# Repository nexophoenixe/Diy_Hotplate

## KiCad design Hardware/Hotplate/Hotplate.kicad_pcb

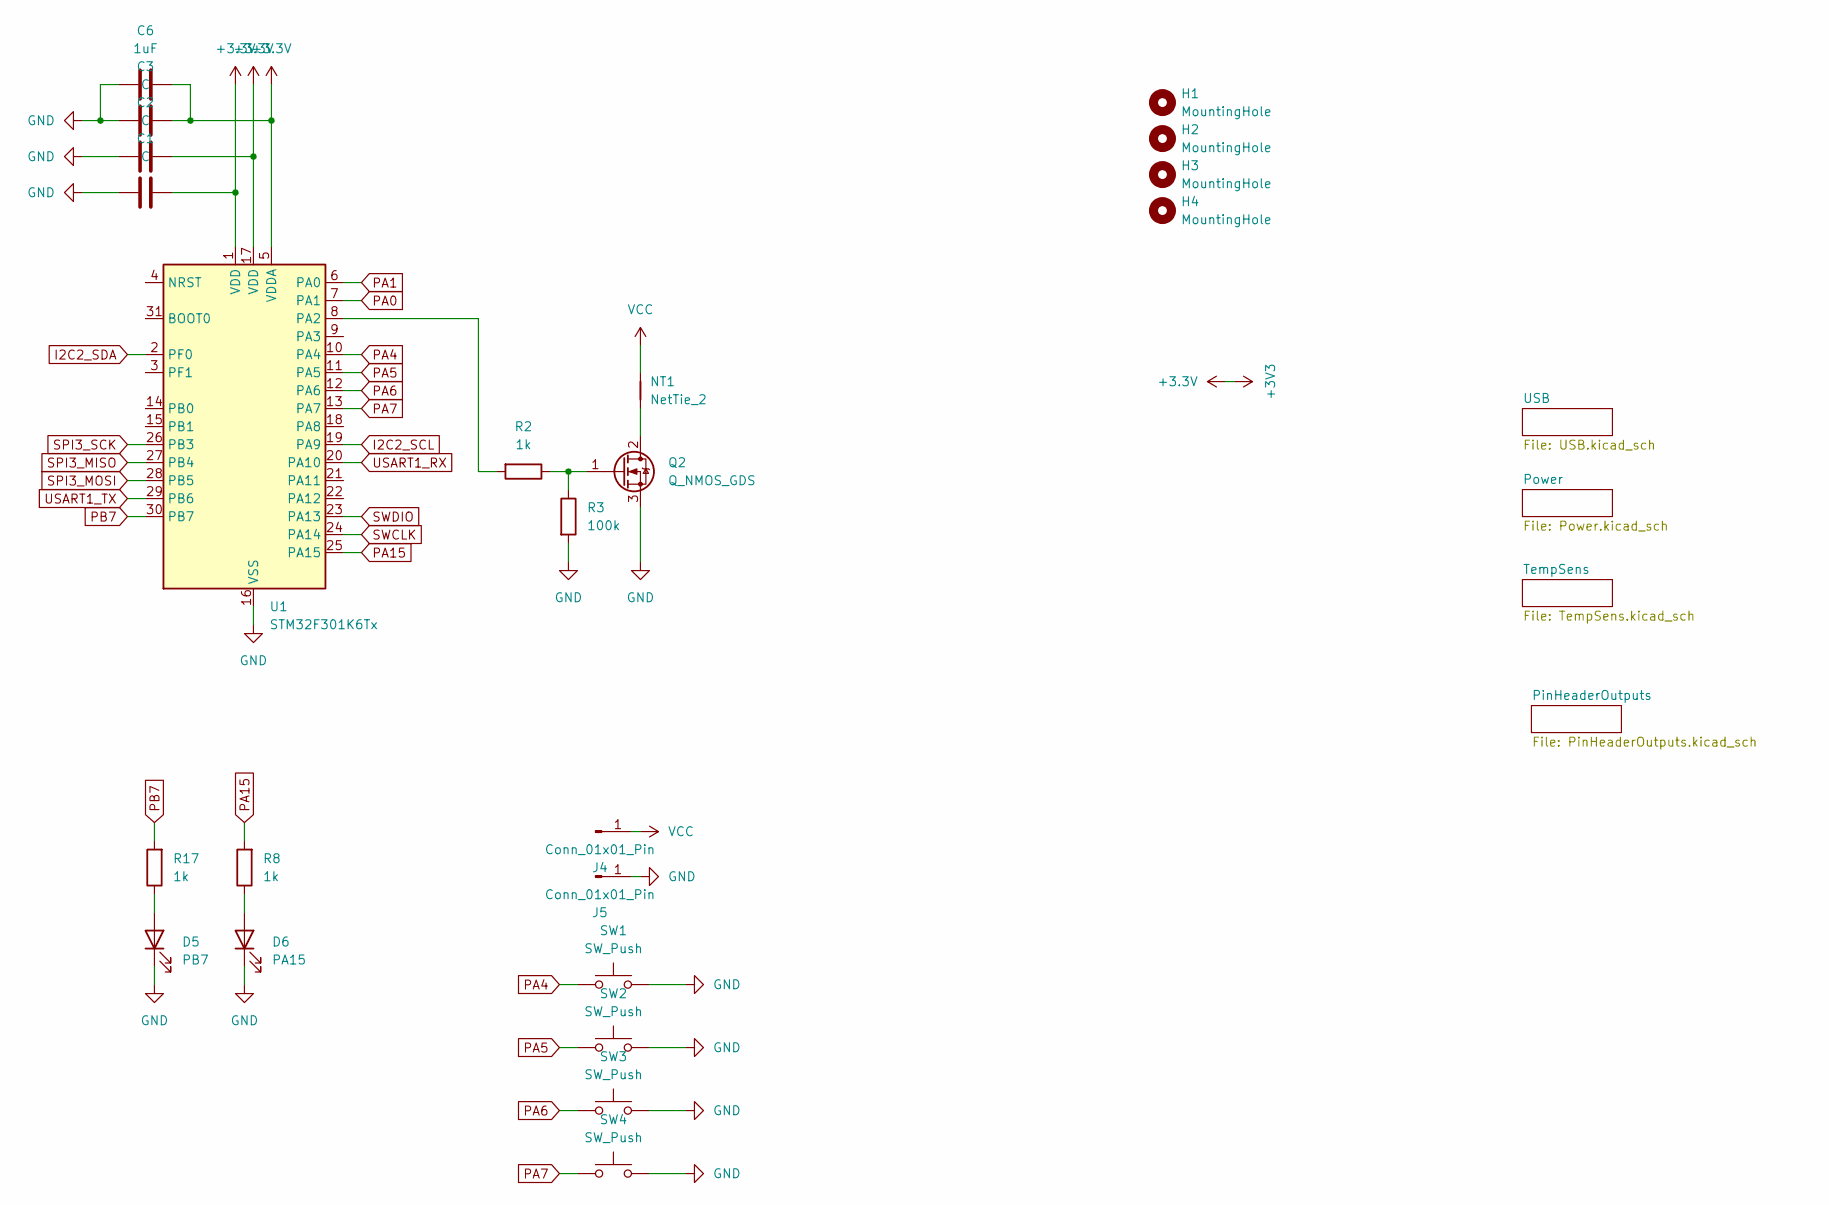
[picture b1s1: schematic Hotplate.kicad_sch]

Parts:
C1, C2, C3: C; C_0603_1608Metric
C6: 1uF; C_0603_1608Metric
D5: PB7; LED_0603_1608Metric_Pad1.05x0.95mm_HandSolder
D6: PA15; LED_0603_1608Metric_Pad1.05x0.95mm_HandSolder
H1, H2, H3, H4: MountingHole; MountingHole_2.7mm_M2.5
J4, J5: Conn_01x01_Pin; SolderWire-1.5sqmm_1x01_D1.7mm_OD3mm
NT1: NetTie_2; NetTie-2_SMD_Pad2.0mm
Q2: Q_NMOS_GDS; TO-252-2
R2: 1k; R_0805_2012Metric
R3: 100k; R_0805_2012Metric
R8, R17: 1k; R_0603_1608Metric_Pad0.98x0.95mm_HandSolder
SW1, SW2, SW3, SW4: SW_Push; SW_PUSH_6mm
U1: STM32F301K6Tx; LQFP-32_7x7mm_P0.8mm

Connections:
+3.3V: C1.2, C2.2, C3.2, C6.2, U1.1 (VDD), U1.5 (VDDA), U1.17 (VDD); also elsewhere on the board
GND: C1.1, C2.1, C3.1, C6.1, D5.1 (K), D6.1 (K), J5.1, Q2.3 (S), R3.2, SW1.2, SW2.2, SW3.2, SW4.2, U1.16 (VSS), U1.32 (VSS); also elsewhere on the board
I2C2_SCL: U1.19 (PA9); also elsewhere on the board
I2C2_SDA: U1.2 (PF0); also elsewhere on the board
unnamed: D5.2 (A), R17.1
unnamed: D6.2 (A), R8.1
unnamed: NT1.1, Q2.2 (D)
unnamed: Q2.1 (G), R2.1, R3.1
unnamed: R2.2, U1.8 (PA2)
PA0: U1.7 (PA1); also elsewhere on the board
PA1: U1.6 (PA0); also elsewhere on the board
PA4: SW1.1, U1.10 (PA4)
PA5: SW2.1, U1.11 (PA5)
PA6: SW3.1, U1.12 (PA6)
PA7: SW4.1, U1.13 (PA7)
PA15: R8.2, U1.25 (PA15)
PB7: R17.2, U1.30 (PB7)
SPI3_MISO: U1.27 (PB4); also elsewhere on the board
SPI3_MOSI: U1.28 (PB5); also elsewhere on the board
SPI3_SCK: U1.26 (PB3); also elsewhere on the board
SWCLK: U1.24 (PA14); also elsewhere on the board
SWDIO: U1.23 (PA13); also elsewhere on the board
USART1_RX: U1.20 (PA10); also elsewhere on the board
USART1_TX: U1.29 (PB6); also elsewhere on the board
VCC: J4.1, NT1.2; also elsewhere on the board

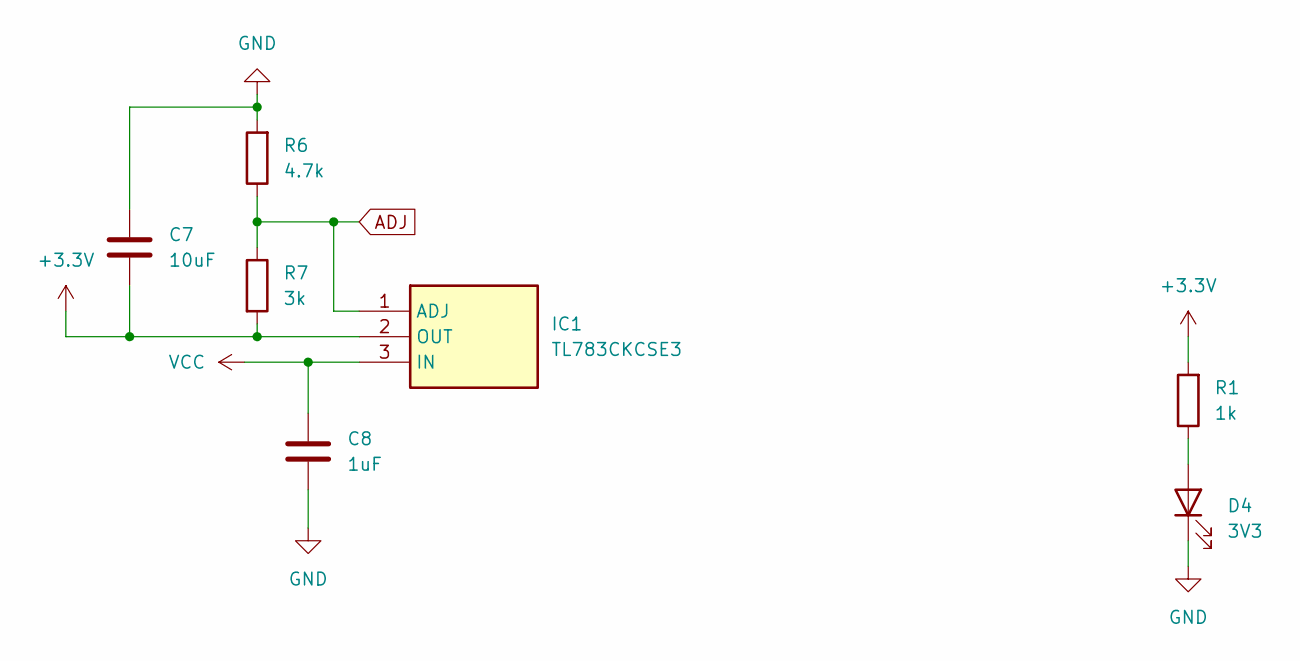
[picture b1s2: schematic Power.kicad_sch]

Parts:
C7: 10uF; C_0805_2012Metric; LCSC C15849
C8: 1uF; C_0805_2012Metric; LCSC C15849
D4: 3V3; LED_0603_1608Metric_Pad1.05x0.95mm_HandSolder
IC1: TL783CKCSE3; TO254P470X1016X1965-3P; Mouser Part Number 595-TL783CKCSE3
R1: 1k; R_0603_1608Metric_Pad0.98x0.95mm_HandSolder
R6: 4.7k; R_0805_2012Metric
R7: 3k; R_0805_2012Metric

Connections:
+3.3V: C7.2, IC1.2 (OUT), R1.2, R7.2; also elsewhere on the board
ADJ: IC1.1 (ADJ), R6.1, R7.1
GND: C7.1, C8.2, D4.1 (K), R6.2; also elsewhere on the board
unnamed: D4.2 (A), R1.1
VCC: C8.1, IC1.3 (IN); also elsewhere on the board

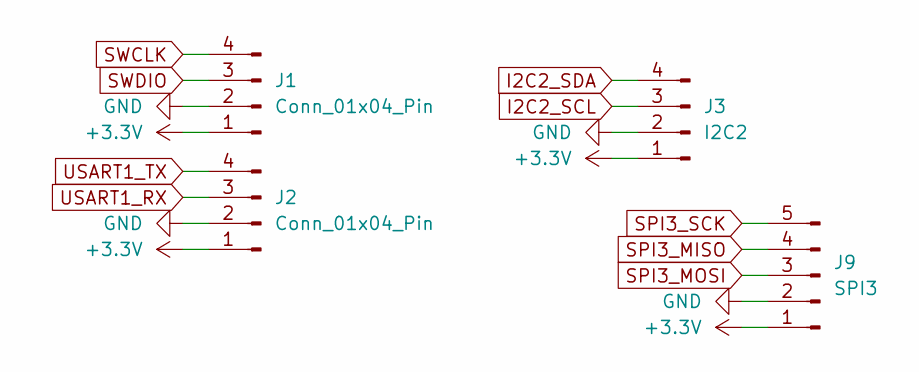
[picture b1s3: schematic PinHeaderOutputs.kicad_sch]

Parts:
J1, J2: Conn_01x04_Pin; PinHeader_1x04_P2.54mm_Vertical
J3: I2C2; PinHeader_1x04_P2.54mm_Vertical
J9: SPI3; PinHeader_1x05_P2.54mm_Vertical

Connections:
+3.3V: J1.1, J2.1, J3.1, J9.1; also elsewhere on the board
GND: J1.2, J2.2, J3.2, J9.2; also elsewhere on the board
I2C2_SCL: J3.3; also elsewhere on the board
I2C2_SDA: J3.4; also elsewhere on the board
SPI3_MISO: J9.4; also elsewhere on the board
SPI3_MOSI: J9.3; also elsewhere on the board
SPI3_SCK: J9.5; also elsewhere on the board
SWCLK: J1.4; also elsewhere on the board
SWDIO: J1.3; also elsewhere on the board
USART1_RX: J2.3; also elsewhere on the board
USART1_TX: J2.4; also elsewhere on the board

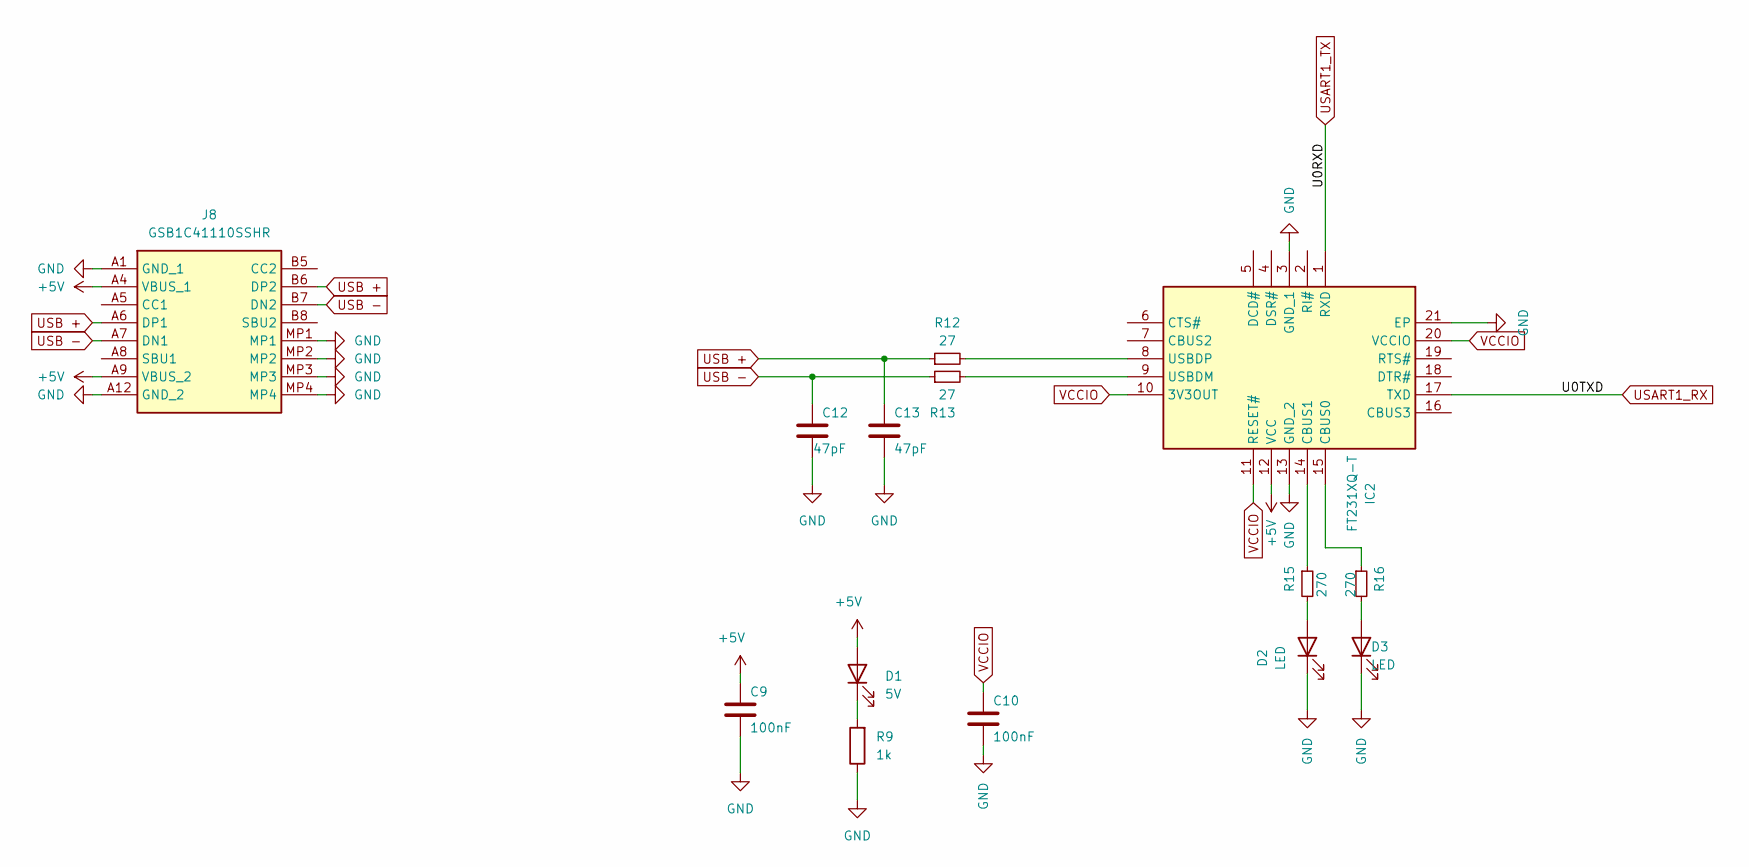
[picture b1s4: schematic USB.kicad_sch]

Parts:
C9, C10: 100nF; C_0603_1608Metric_Pad1.08x0.95mm_HandSolder
C12, C13: 47pF; C_0603_1608Metric_Pad1.08x0.95mm_HandSolder
D1: 5V; LED_0603_1608Metric_Pad1.05x0.95mm_HandSolder
D2, D3: LED; LED_0603_1608Metric_Pad1.05x0.95mm_HandSolder
IC2: FT231XQ-T; QFN50P400X400X80-21N; Mouser Part Number 895-FT231XQ-T
J8: GSB1C41110SSHR; Manufacturer_Part_Number GSB1C41110SSHR
R9: 1k; R_0603_1608Metric_Pad0.98x0.95mm_HandSolder
R12, R13: 27; R_0603_1608Metric_Pad0.98x0.95mm_HandSolder
R15, R16: 270; R_0603_1608Metric_Pad0.98x0.95mm_HandSolder

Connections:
+5V: C9.1, D1.2 (A), IC2.12 (VCC), J8.A4 (VBUS_1), J8.A9 (VBUS_2)
GND: C9.2, C10.2, C12.2, C13.2, D2.1 (K), D3.1 (K), IC2.3 (GND_1), IC2.13 (GND_2), IC2.21 (EP), J8.A1 (GND_1), J8.A12 (GND_2), J8.MP1, J8.MP2, J8.MP3, J8.MP4, R9.1; also elsewhere on the board
unnamed: D1.1 (K), R9.2
unnamed: D2.2 (A), R15.2
unnamed: D3.2 (A), R16.2
unnamed: IC2.15 (CBUS0), R16.1
unnamed: IC2.14 (CBUS1), R15.1
unnamed: IC2.9 (USBDM), R13.2
unnamed: IC2.8 (USBDP), R12.2
USART1_RX: IC2.17 (TXD); also elsewhere on the board
USART1_TX: IC2.1 (RXD); also elsewhere on the board
USB +: C13.1, J8.A6 (DP1), J8.B6 (DP2), R12.1
USB -: C12.1, J8.A7 (DN1), J8.B7 (DN2), R13.1
VCCIO: C10.1, IC2.10 (3V3OUT), IC2.11 (RESET#), IC2.20 (VCCIO)

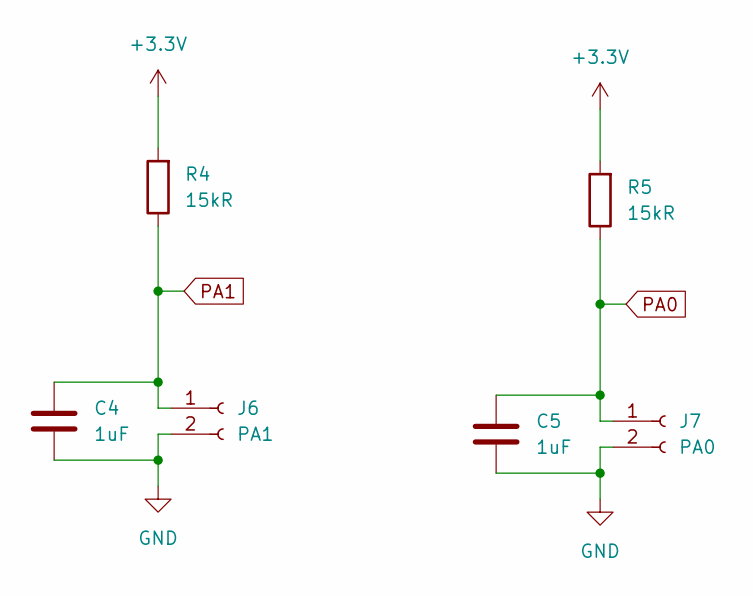
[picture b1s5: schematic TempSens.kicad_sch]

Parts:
C4, C5: 1uF; C_0603_1608Metric; LCSC C15849
J6: PA1; JST_EH_B2B-EH-A_1x02_P2.50mm_Vertical
J7: PA0; JST_EH_B2B-EH-A_1x02_P2.50mm_Vertical
R4, R5: 15kR; R_0805_2012Metric; LCSC C17475

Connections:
+3.3V: R4.2, R5.2; also elsewhere on the board
GND: C4.2, C5.2, J6.2, J7.2; also elsewhere on the board
PA0: C5.1, J7.1, R5.1; also elsewhere on the board
PA1: C4.1, J6.1, R4.1; also elsewhere on the board

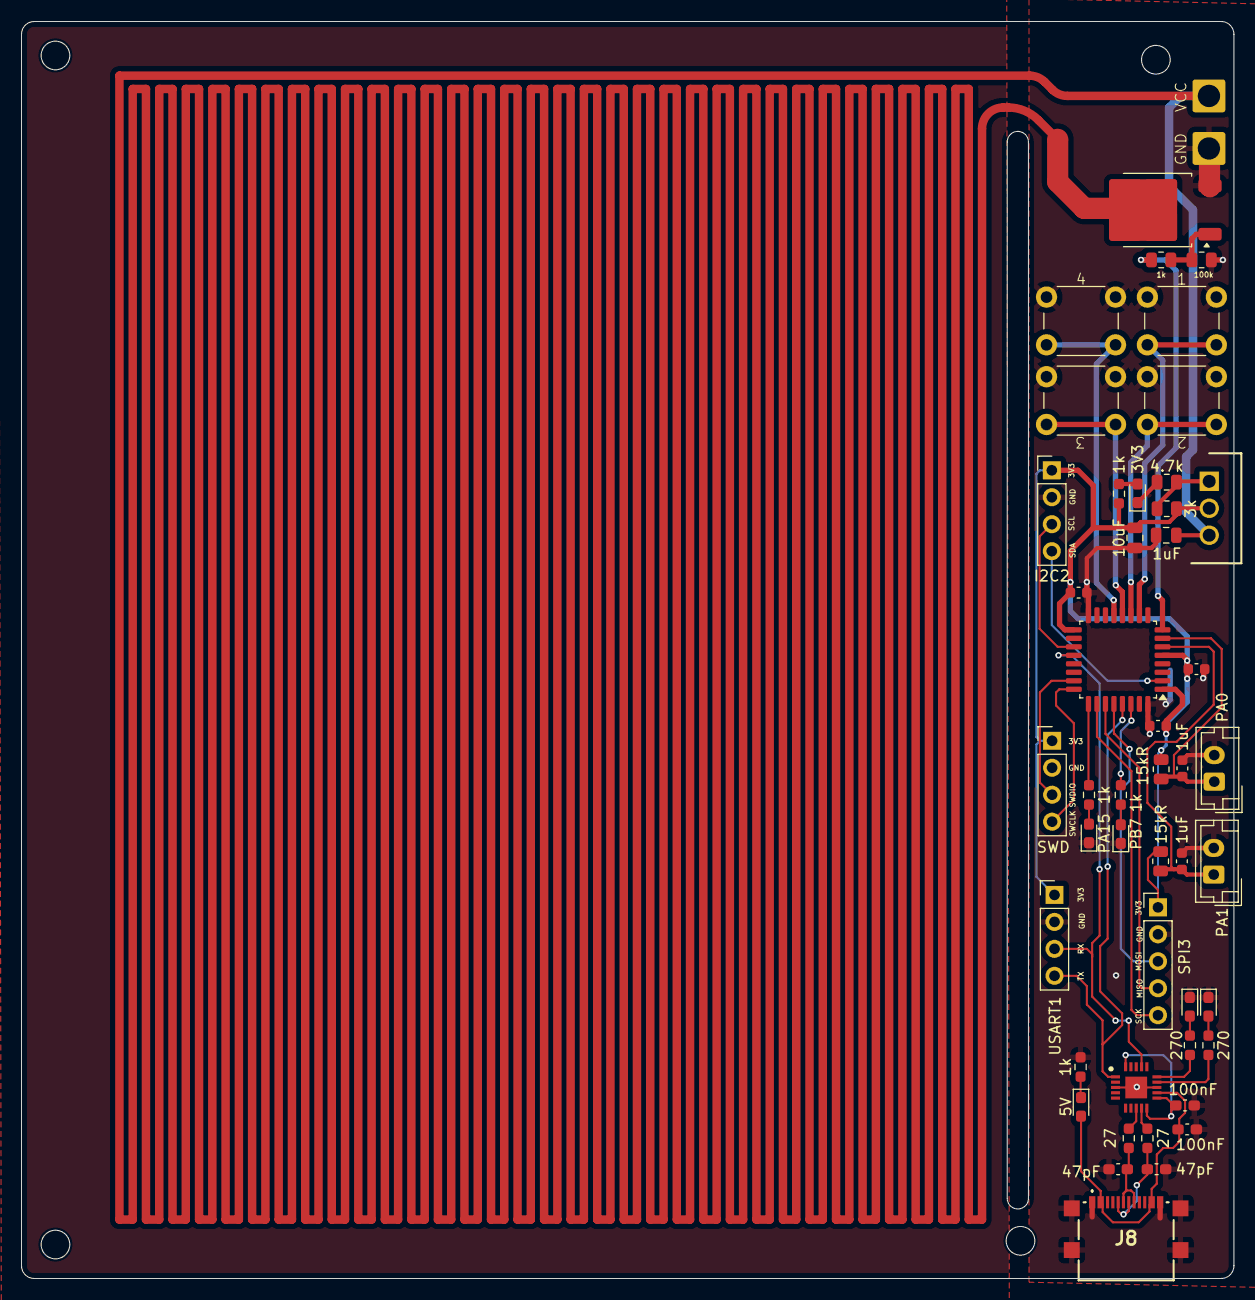
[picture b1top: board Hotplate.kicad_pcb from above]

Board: 2 copper layers, 114.2 x 118.4 mm, 54 parts (1 on the bottom side), 38 nets.

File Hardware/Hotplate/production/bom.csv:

Designator,Footprint,Quantity,Value,LCSC Part #
"C1, C2, C3",0603,3,C,
"C10, C9",0603,2,100nF,
"C12, C13",0603,2,47pF,
"C4, C5",0603,2,1uF,C15849
C6,0603,1,1uF,
C7,0805,1,10uF,C15849
C8,0805,1,1uF,C15849
D1,0603,1,5V,
"D2, D3",0603,2,LED,
D4,0603,1,3V3,
D5,0603,1,PB7,
D6,0603,1,PA15,
IC1,TO254P470X1016X1965-3P,1,TL783CKCSE3,
IC2,QFN50P400X400X80-21N,1,FT231XQ-T,
"J1, J2",PinHeader_1x04_P2.54mm_Vertical,2,Conn_01x04_Pin,
J3,PinHeader_1x04_P2.54mm_Vertical,1,I2C2,
"J4, J5",SolderWire-1.5sqmm_1x01_D1.7mm_OD3mm,2,Conn_01x01_Pin,
J8,GSB1C41110SSHR,1,GSB1C41110SSHR,
J9,PinHeader_1x05_P2.54mm_Vertical,1,SPI3,
Q2,TO-252-2,1,Q_NMOS_GDS,
"R1, R17, R8, R9",0603,4,1k,
"R12, R13",0603,2,27,
"R15, R16",0603,2,270,
R2,0805,1,1k,
R3,0805,1,100k,
"R4, R5",0805,2,15kR,C17475
R6,0805,1,4.7k,
R7,0805,1,3k,
"SW1, SW2, SW3, SW4",SW_PUSH_6mm,4,SW_Push,
U1,LQFP-32_7x7mm_P0.8mm,1,STM32F301K6Tx,

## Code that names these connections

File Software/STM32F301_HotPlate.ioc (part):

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Mcu.Name=STM32F301K(6-8)Tx
Mcu.Package=LQFP32
Mcu.UserName=STM32F301K6Tx
PA0.Mode=IN1-Single-Ended
PA0.Signal=ADC1_IN1
PA1.Mode=IN2-Single-Ended
PA1.Signal=ADC1_IN2
PA10.Mode=Asynchronous
PA10.Signal=USART1_RX
PA13.Mode=Serial_Wire
PA13.Signal=SYS_JTMS-SWDIO
PA14.Mode=Serial_Wire
PA14.Signal=SYS_JTCK-SWCLK
PA2.Signal=S_TIM2_CH3
PA4.GPIOParameters=GPIO_Label
PA4.GPIO_Label=B1
PA4.Signal=GPIO_Output
PA5.GPIOParameters=GPIO_Label
PA5.GPIO_Label=B2
PA5.Signal=GPIO_Output
PA6.Signal=GPIO_Input
PA7.GPIOParameters=GPIO_Label
PA7.GPIO_Label=B4
PA7.Signal=GPIO_Input
PA9.Mode=I2C
PA9.Signal=I2C2_SCL
PB3.Mode=Full_Duplex_Master
PB3.Signal=SPI3_SCK
PB4.Mode=Full_Duplex_Master
PB4.Signal=SPI3_MISO
PB5.Mode=Full_Duplex_Master
PB5.Signal=SPI3_MOSI
PB6.Mode=Asynchronous
PB6.Signal=USART1_TX
PF0-OSC_IN.Mode=I2C
PF0-OSC_IN.Signal=I2C2_SDA
PF1-OSC_OUT.Signal=GPXTI1
RCC.HSEPLLFreq_Value=8000000
RCC.HSE_VALUE=8000000
RCC.SYSCLKFreq_VALUE=64000000
RCC.SYSCLKSourceVirtual=RCC_SYSCLKSOURCE_PLLCLK
board=custom

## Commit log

2025-12-28 add right dir
